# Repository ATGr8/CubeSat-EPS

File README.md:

# CubeSat-EPS

I am making a design for custom 2U CubeSat EPS, which is simple to implement and is open source. This is because most of the EPS available off the shelf are sold
without much information of the actual circuitry of the board and are very expensive. 

I will be uploading my progress to github as I go - to sorta keep me accountable

The KiCAD Schematic is a litlle rough right now and the file manaegement is not the best, but I will be working on fixing them soon. If you need help with understanding anything feel free to reach out to me

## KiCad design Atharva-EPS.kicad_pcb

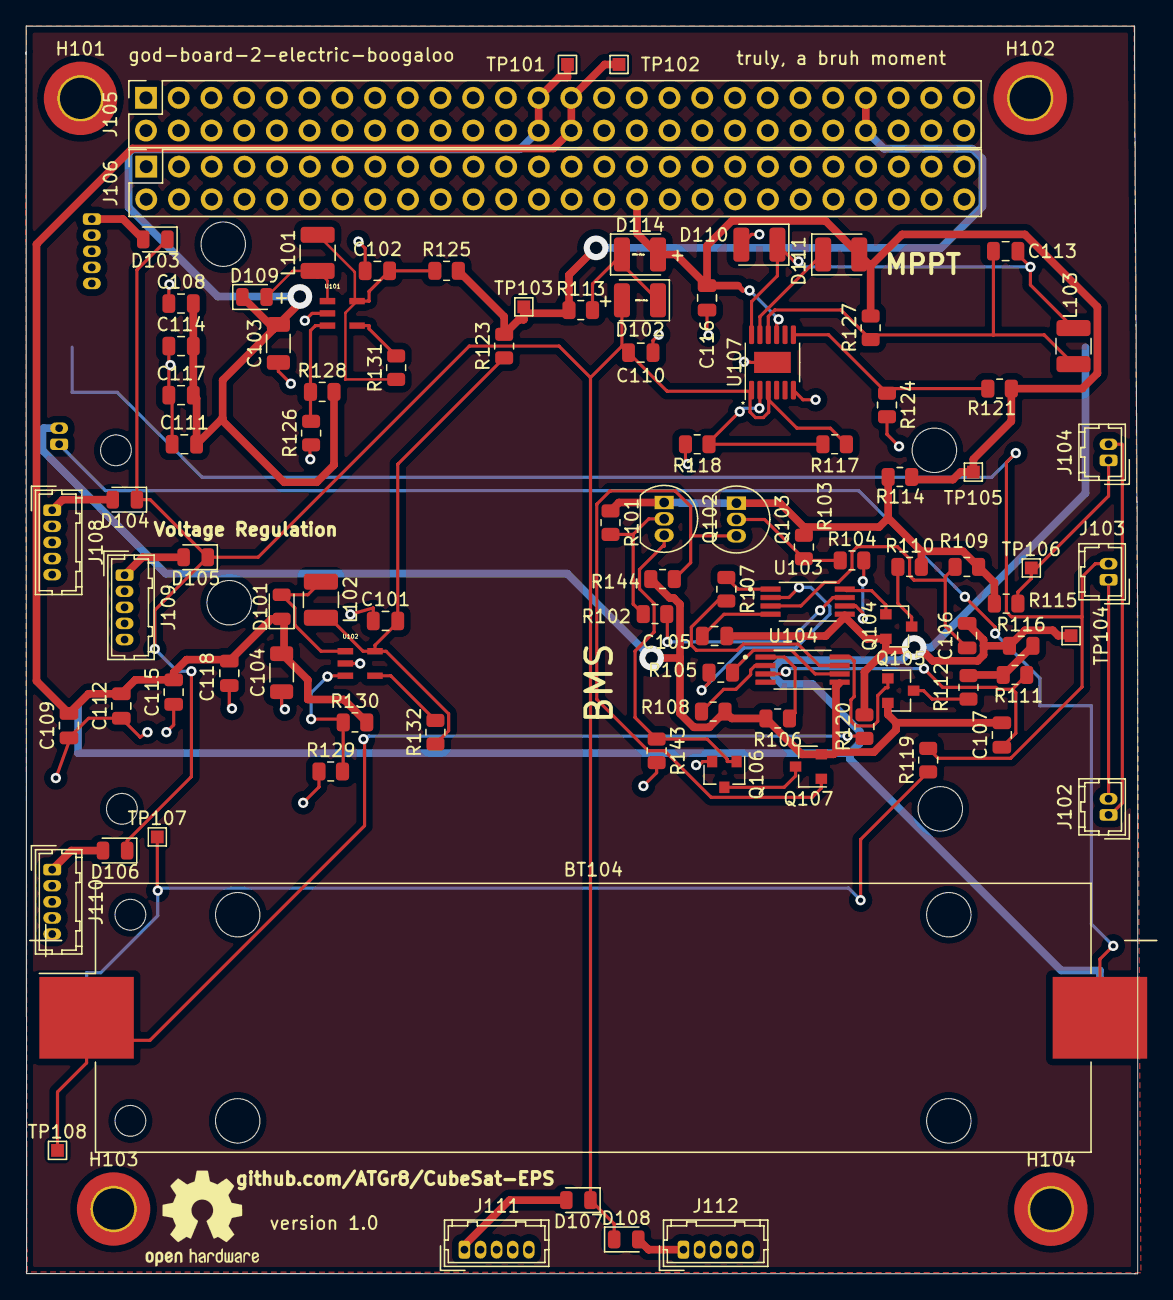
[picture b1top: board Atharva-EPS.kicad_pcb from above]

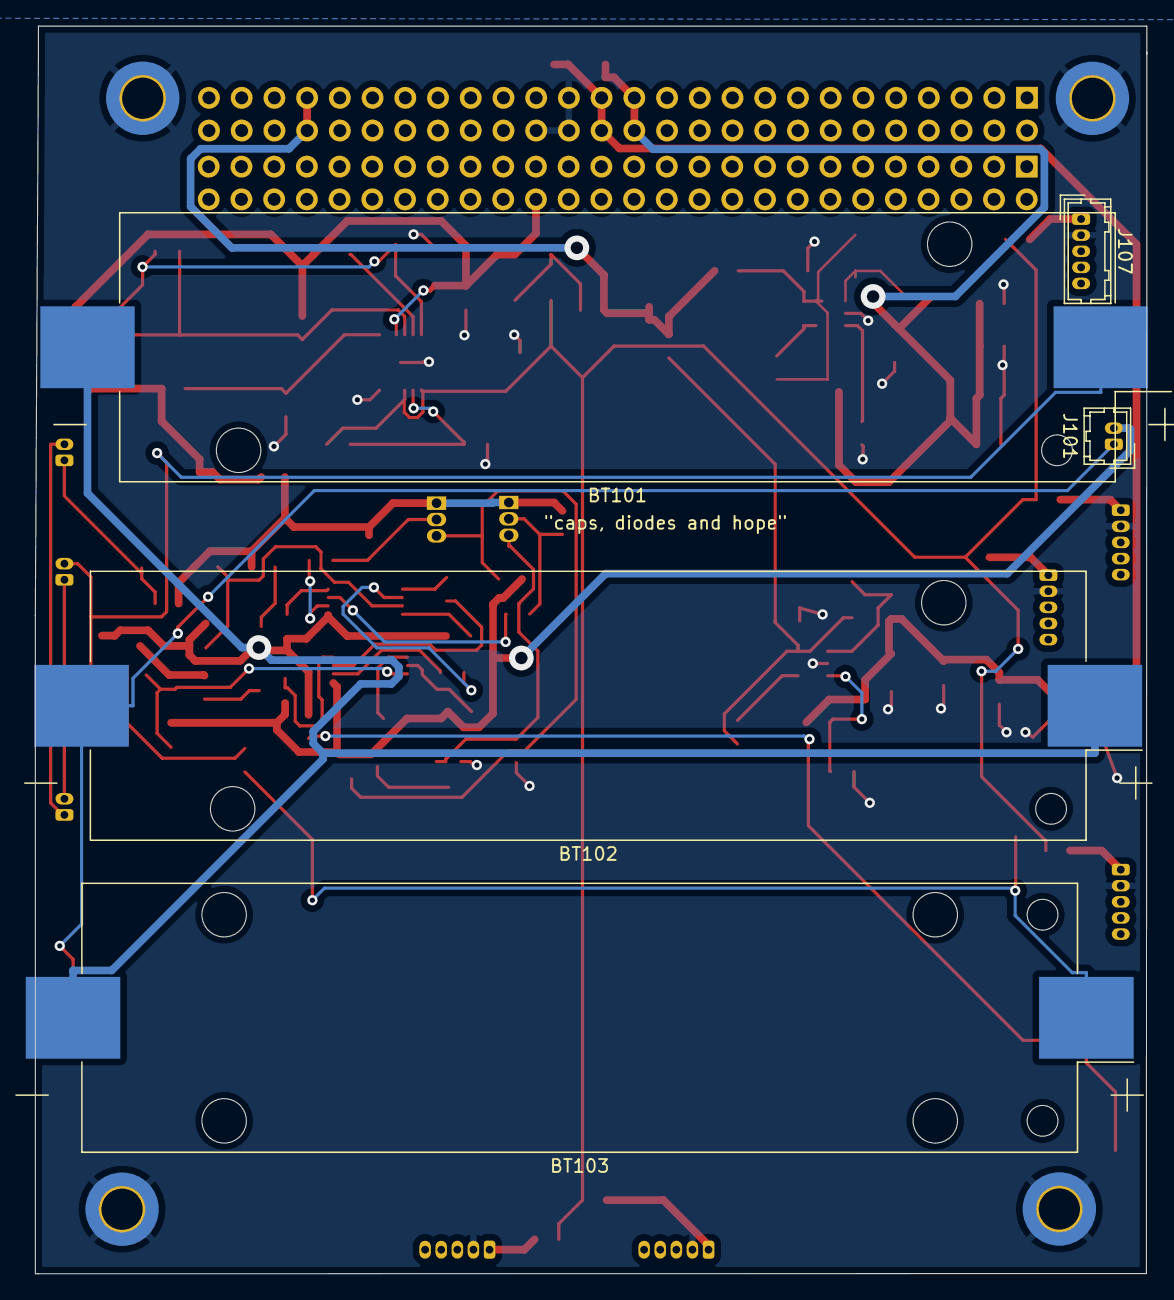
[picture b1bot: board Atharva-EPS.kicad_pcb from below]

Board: 2 copper layers, 86.3 x 96.9 mm, 105 parts (5 on the bottom side), 57 nets.

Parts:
BT101, BT102, BT103, BT104: Battery_Cell; BatteryHolder_Keystone_1042_1x18650
C101, C102, C106, C107: 0.1uF; C_0805_2012Metric
C103, C104: 4.7uF; C_1206_3216Metric
C105: 0.01uF; C_0805_2012Metric
C108, C109, C111, C112, C114, C115, C117, C118: Test; C_0805_2012Metric
C110, C116: 10uF; C_0805_2012Metric
C113: 1uF; C_0805_2012Metric
D101, D103, D104, D105, D106, D107, D108, D109: D_Schottky; D_0805_2012Metric
D102, D110, D114: D_Schottky; D_1210_3225Metric
D111: D; D_1210_3225Metric
H101, H102, H103, H104: MountingHole_Pad; MountingHole_3.2mm_M3_ISO7380_Pad_TopBottom
J101, J102, J103, J104: Conn_01x02_Female; Hirose_DF13-02P-1.25DSA_1x02_P1.25mm_Vertical
J105, J106: Conn_02x26_Odd_Even; PinSocket_2x26_P2.54mm_Vertical
J107, J108, J109, J110, J111, J112: Conn_01x05_Female; Hirose_DF13-05P-1.25DSA_1x05_P1.25mm_Vertical
L101, L102, L103: 10uH; L_1210_3225Metric
Q102, Q103: 2N3906; TO-92_Inline
Q104, Q105, Q106, Q107: IRLML2060; SOT-23
R101, R103, R143, R144: 1M; R_0805_2012Metric
R102, R104: 510k; R_0805_2012Metric
R105, R106, R107, R108: 1k; R_0805_2012Metric
R109, R111: 470; R_0805_2012Metric
R110, R112: 51; R_0805_2012Metric
R113, R114, R115, R116, R119, R120, R123, R125: 0; R_0805_2012Metric
R117: 530k; R_0805_2012Metric
R118: 100k; R_0805_2012Metric
R121: 542k; R_0805_2012Metric
R124: 459k; R_0805_2012Metric
R126, R129: 13.3k; R_0805_2012Metric
R127: 0.05; R_0805_2012Metric
R128: 39.688k; R_0805_2012Metric
R130: 21.672k; R_0805_2012Metric
R131, R132: 121k; R_0805_2012Metric
TP101, TP102, TP103, TP104, TP105, TP106, TP107, TP108: TestPoint; TestPoint_Pad_1.0x1.0mm
U101, U102: LT1930ES5TRMPBF; SOT-5_S
U103, U104: S-8209AXXT; SOP65P640X120-8N
U107: LT3652EMSE; MSOP-12-1EP_3x4mm_P0.65mm_EP1.65x2.85mm

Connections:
+3V3: C104.2, C109.2, C112.2, C115.2, C118.2, D101.1 (K), J105.27, J105.28, R130.2, TP102.1
+5V: C103.2, C108.2, C111.2, C114.2, C117.2, D109.1 (K), J105.25, J105.26, R128.2, TP101.1
+BATT: J105.45, J105.46, R113.1, R123.2, R125.2, TP103.1
/+Batt_1: Q102.1 (E), Q103.1 (E), R101.1, R103.1, R109.1, R110.1, R114.1, R115.2
/+Batt_2: R111.1, R112.1, R116.2
/-Batt_1: BT101.2 (-), BT102.1 (+), BT103.2 (-), C105.1, C106.2, Q104.2 (S), R116.1, R120.2, TP104.1, U103.5 (VSS)
/-Batt_2: C107.2, J101.2, Q105.2 (S), Q107.2 (S), R106.2, R108.2, R144.2, U104.5 (VSS)
/Solar_1: D103.2 (A), J107.1
/Solar_2: D104.2 (A), J108.1
/Solar_3: D105.2 (A), J109.1
/Solar_4: D106.2 (A), J110.1
/Solar_5: D107.2 (A), J111.1
/Solar_6: D108.2 (A), J112.1
Batt_in: C116.1, D111.2 (A), D114.2 (A), J106.32, R114.2, R121.2, R127.2, TP105.1, U107.9 (BAT)
GND: C101.1, C102.1, C103.1, C104.1, C108.1, C109.1, C110.2, C111.1, C112.1, C114.1, C115.1, C116.2, C117.1, C118.1, D110.2 (A), H101.1, H102.1, H103.1, H104.1, J105.29, J105.30, J105.32, J107.2, J108.2, J109.2, J110.2, J111.2, J112.2, Q106.2 (S), R118.2, R124.2, R126.1, R129.1, R143.2, U101.2 (GND), U102.2 (GND), U107.6 (TIMER), U107.13 (GND)
MPPT_OUT: D102.1 (K), D114.1 (K), R113.2
unnamed: BT101.1 (+), J103.2, R119.2
unnamed: BT102.2 (-), BT104.2 (-), J101.1
unnamed: BT103.1 (+), R119.1, TP107.1
unnamed: BT104.1 (+), R120.1, TP108.1
unnamed: C101.2, L102.2, R123.1, R132.1, U102.5 (VIN)
unnamed: C102.2, L101.2, R125.1, R131.1, U101.5 (VIN)
unnamed: C105.2, U103.4 (CDT)
unnamed: C106.1, R109.2, U103.3 (VDD)
unnamed: C107.1, R111.2, U104.3 (VDD)
unnamed: C113.1, D110.1 (K), L103.1, U107.12 (SW)
unnamed: C113.2, L103.2, R127.1, U107.10 (SENSE)
unnamed: D101.2 (A), L102.1, U102.1 (SW)
unnamed: D109.2 (A), L101.1, U101.1 (SW)
unnamed: D111.1 (K), U107.11 (BOOST)
unnamed: J102.1, J104.2
unnamed: J102.2, J103.1
unnamed: J104.1, R115.1, TP106.1
unnamed: Q102.2 (B), R101.2, R102.1
unnamed: Q102.3 (C), Q106.1 (G), R143.1
unnamed: Q103.2 (B), R103.2, R104.1
unnamed: Q103.3 (C), Q107.1 (G), R144.1
unnamed: Q104.1 (G), U103.8 (CB)
unnamed: Q104.3 (D), R110.2
unnamed: Q105.1 (G), U104.8 (CB)
unnamed: Q105.3 (D), R112.2
unnamed: Q106.3 (D), Q107.3 (D)
unnamed: R102.2, U103.7 (CO)
unnamed: R104.2, U103.6 (DO)
unnamed: R105.1, U103.2 (CTLD)
unnamed: R105.2, U104.6 (DO)
unnamed: R106.1, U104.1 (CTLC)
unnamed: R107.1, U103.1 (CTLC)
unnamed: R107.2, U104.7 (CO)
unnamed: R108.1, U104.2 (CTLD)
unnamed: R117.2, R118.1, U107.2 (VIN_REG)
unnamed: R121.1, R124.1, U107.7 (VFB)
unnamed: R131.2, U101.4 (*SHDN)
unnamed: R132.2, U102.4 (*SHDN)
unnamed: R126.2, R128.1, U101.3 (FB)
unnamed: R129.2, R130.1, U102.3 (FB)
Solar_Out: C110.1, D102.2 (A), D103.1 (K), D104.1 (K), D105.1 (K), D106.1 (K), D107.1 (K), D108.1 (K), R117.1, U107.1 (VIN), U107.3 (~SHDN)

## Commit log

2022-09-03 more progress on the BMS schematic
2022-09-03 add comments to BMS schematic
2022-09-04 added fuel guage circuit schematic
2022-09-06 fixed battery configuration error
2022-09-06 added documentation for the chips used, in form of datasheets
2022-09-10 Added MPPT and made a 2s2p battery pack - corrected BMS and fuel guage accordingly
2022-09-12 Added inhibit logic and made the schematic a lot cleaner
2022-09-16 Improved logic for charging by charging through the BMS and fleshed out solar panel MPPT logic
2022-09-16 minor fixes
2022-09-17 Placed footprints on PCB, improvements on schematic
2022-09-17 combined all MPPTs into one
2022-09-18 added simulations
2022-09-18 Changed the schottky diode logic
2022-09-18 added some traces, placed connectors
2022-09-18 More manual routing
2022-09-19 Finished V1 pcb (just found out the voltage reg is wrong)
2022-09-19 New buck booster logic for voltage regulation
2022-09-19 added kicad footprints
2022-09-21 redesigned the board layout, traces and addded images
2022-09-22 added diodes to all solar panel input - preventing shorts between parallel solar panels
2022-09-23 EPS version 1,0
2022-09-26 EPS version 1.0 - fixed minor error of having placed the reistors at the wrong spot in the buck boost
2022-11-01 Added recent schematic

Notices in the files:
parts and their libraries:
COPYRIGHT: Copyright C 2016 Accelerated Designs. All rights reserved
